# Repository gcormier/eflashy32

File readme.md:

# eflashy32

eflashy32 is a USB Type-C, CP2102N serial interface targeting ESP devices. It has a 500mA resettable fuse, ESD protection, and a switch to choose if you want to send 3.3V to the device or not.

While Micro USB is still everywhere, USB-C needs to start taking over. My new laptop has only USB-C ports, and I wanted to have one less dongle.

The board is designed in a such a manner to allow either a 2.54mm pitch 1x6 pin header, 1.27mm pitch header, or pogo pins!

## Tindie
Available <a href="https://www.tindie.com/products/gcormier/eflashy32/">for purchase on Tindie</a>.

## Design Goals
- [ ] USB Type C
- [ ] Good serial chip with no drivers needed and no <a href="https://hackaday.com/2016/02/01/ftdi-drivers-break-fake-chips-again/">malware</a>
- [ ] Switch to toggle providing power to device
- [ ] Small
- [ ] Ability to use pogo pins

## Notes
I added the ubiquitous 2.54mm pitch header for classic scenarios, using either a 6 pin header, or using 6 pogo pins. On the back side is a similar 1.27mm pitch header for miniature designs.

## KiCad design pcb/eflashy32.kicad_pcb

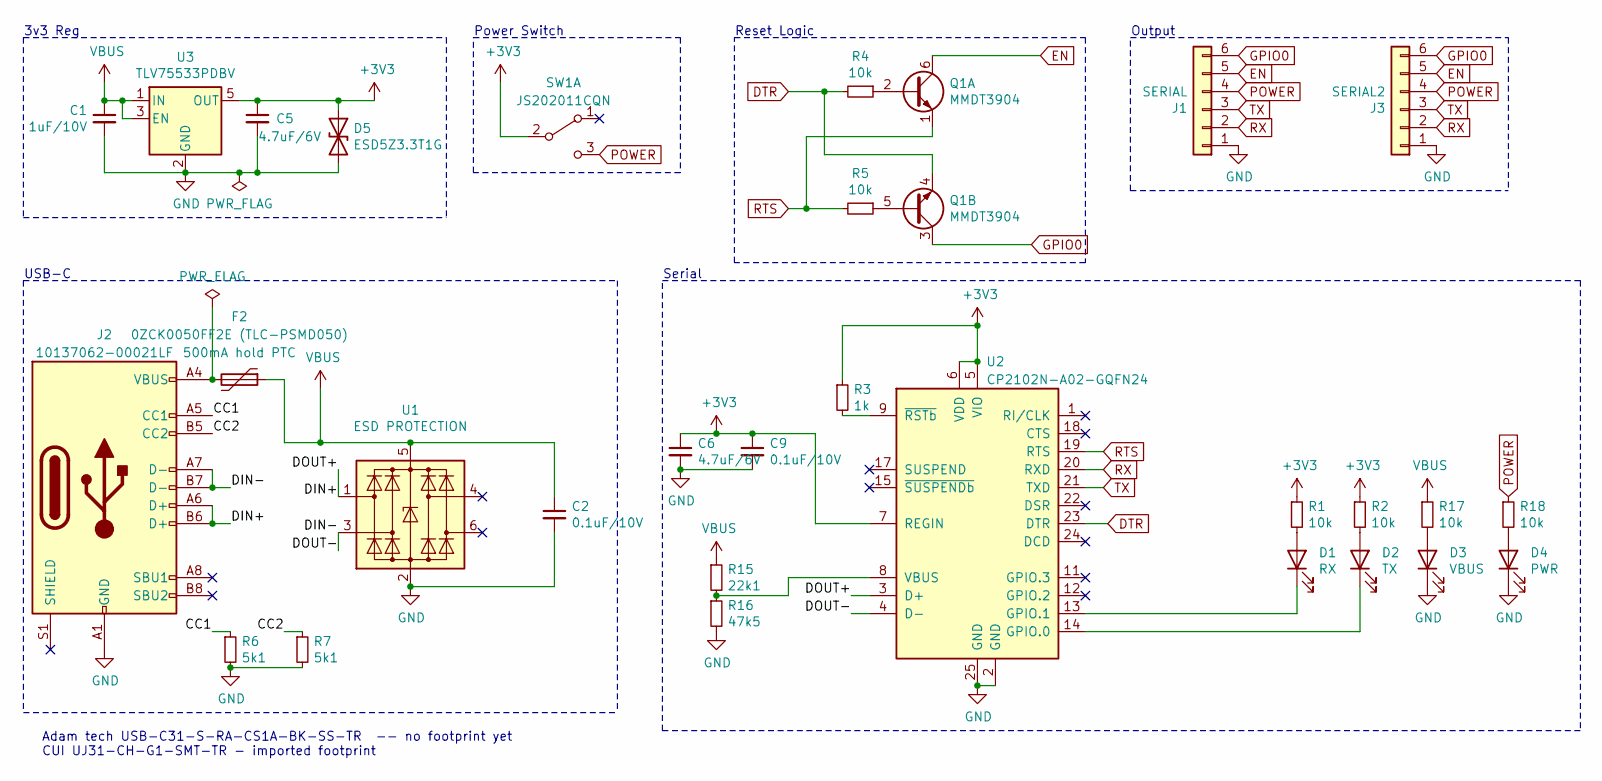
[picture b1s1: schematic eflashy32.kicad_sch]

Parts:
C1: 1uF/10V; C_0805_2012Metric; LCSC C28323
C2, C9: 0.1uF/10V; C_0805_2012Metric; LCSC C49678
C5, C6: 4.7uF/6V; C_0805_2012Metric; LCSC C1779
D1: RX; LED_0805_2012Metric; LCSC C2293
D2: TX; LED_0805_2012Metric; LCSC C2293
D3: VBUS; LED_0805_2012Metric; LCSC C2297
D4: PWR; LED_0805_2012Metric; LCSC C84256
D5: ESD5Z3.3T1G; D_SOD-523; LCSC C61148
F2: 0ZCK0050FF2E (TLC-PSMD050); Fuse_0805_2012Metric_Pad1.15x1.40mm_HandSolder; LCSC C261942
J1: SERIAL; 2.54mmedge; LCSC DNP
J2: 10137062-00021LF; USBC-Amphenol-10137062-00021LF; LCSC C388659
J3: SERIAL2; 1.27mmedge; LCSC DNP
Q1: MMDT3904; SOT-363_SC-70-6; LCSC C83572
R1, R2, R4, R5, R17, R18: 10k; R_0805_2012Metric; LCSC C17414
R3: 1k; R_0805_2012Metric; LCSC C17513
R6, R7: 5k1; R_0805_2012Metric; LCSC C27834
R15: 22k1; R_0805_2012Metric; LCSC C17560
R16: 47k5; R_0805_2012Metric; LCSC C17713
SW1: JS202011CQN; SW_CuK_JS202011CQN_DPDT_Straight; LCSC DNP
U1: ESD PROTECTION; SOT-23-6; LCSC C294963
U2: CP2102N-A02-GQFN24; QFN-24-1EP_4x4mm_P0.5mm_EP2.6x2.6mm; LCSC C969151
U3: TLV75533PDBV; SOT-23-5; LCSC C255621 C404027

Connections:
+3V3: C5.1, C6.1, C9.1, D5.1 (A1), R1.1, R2.1, R3.1, SW1.2 (B), U2.5 (VIO), U2.6 (VDD), U2.7 (REGIN), U3.5 (OUT)
/CC1: J2.A5 (CC1), R6.1
/CC2: J2.B5 (CC2), R7.1
/DIN+: J2.A6 (D+), J2.B6 (D+), U1.1 (I/O1), U2.3 (D+)
/DIN-: J2.A7 (D-), J2.B7 (D-), U1.3 (I/O2), U2.4 (D-)
DTR: Q1.4 (E2), R4.2, U2.23 (DTR)
EN: J1.5, J3.5, Q1.6 (C1)
GND: C1.2, C2.2, C5.2, C6.2, C9.2, D3.1 (K), D4.1 (K), D5.2 (A2), J1.1, J2.A1 (GND), J2.A12 (GND), J2.B1 (GND), J2.B12 (GND), J3.1, R6.2, R7.2, R16.2, U1.2 (GND), U2.2 (GND), U2.25 (GND), U3.2 (GND)
GPIO0: J1.6, J3.6, Q1.3 (C2)
unnamed: D1.1 (K), U2.13 (GPIO.1)
unnamed: D1.2 (A), R1.2
unnamed: D2.1 (K), U2.14 (GPIO.0)
unnamed: D2.2 (A), R2.2
unnamed: D3.2 (A), R17.2
unnamed: D4.2 (A), R18.2
unnamed: F2.2, J2.A4 (VBUS), J2.A9 (VBUS), J2.B4 (VBUS), J2.B9 (VBUS)
unnamed: Q1.2 (B1), R4.1
unnamed: Q1.5 (B2), R5.1
unnamed: R3.2, U2.9 (~RSTb)
unnamed: R15.2, R16.1, U2.8 (VBUS)
POWER: J1.4, J3.4, R18.1, SW1.3 (C)
RTS: Q1.1 (E1), R5.2, U2.19 (RTS)
RX: J1.2, J3.2, U2.20 (RXD)
TX: J1.3, J3.3, U2.21 (TXD)
VBUS: C1.1, C2.1, F2.1, R15.1, R17.1, U1.5 (VBUS), U3.1 (IN), U3.3 (EN)

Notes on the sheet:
3v3 Reg
USB-C
Adam tech USB-C31-S-RA-CS1A-BK-SS-TR -- no footprint yet CUI UJ31-CH-G1-SMT-TR - imported footprint
Power Switch
Serial
Reset Logic
Output

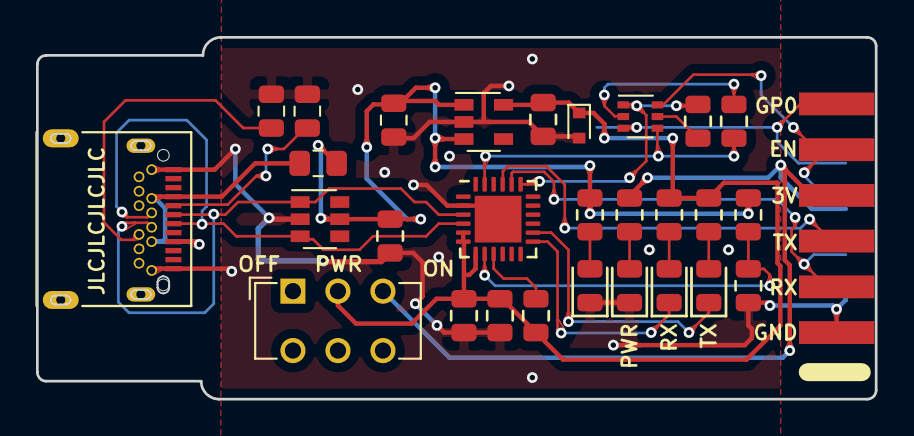
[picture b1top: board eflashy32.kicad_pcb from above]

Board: 2 copper layers, 46.6 x 20.1 mm, 30 parts (1 on the bottom side), 25 nets.

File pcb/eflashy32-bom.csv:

Comment,Designator,Footprint,LCSC
"1uF/10V","C1","Capacitor_SMD:C_0805_2012Metric","C28323"
"0.1uF/10V","C2,C9","Capacitor_SMD:C_0805_2012Metric","C49678"
"4.7uF/6V","C5,C6","Capacitor_SMD:C_0805_2012Metric","C1779"
"RX","D1","LED_SMD:LED_0805_2012Metric","C2293"
"TX","D2","LED_SMD:LED_0805_2012Metric","C2293"
"VBUS","D3","LED_SMD:LED_0805_2012Metric","C2297"
"PWR","D4","LED_SMD:LED_0805_2012Metric","C84256"
"ESD5Z3.3T1G","D5","Diode_SMD:D_SOD-523","C61148"
"0ZCK0050FF2E (TLC-PSMD050)","F2","Fuse:Fuse_0805_2012Metric_Pad1.15x1.40mm_HandSolder","C261942"
"SERIAL","J1","!Greg:2.54mmedge","DNP"
"10137062-00021LF","J2","!Greg:USBC-Amphenol-10137062-00021LF","DNP"
"SERIAL2","J3","!Greg:1.27mmedge","DNP"
"MMDT3904","Q1","Package_TO_SOT_SMD:SOT-363_SC-70-6","C83572"
"22k1","R15","Resistor_SMD:R_0805_2012Metric","C17560"
"47k5","R16","Resistor_SMD:R_0805_2012Metric","C17713"
"5k1","R6,R7,R17","Resistor_SMD:R_0805_2012Metric","C17513"
"1k","R1,R2,R3,R18","Resistor_SMD:R_0805_2012Metric","C17414"
"10k","R4,R5","Resistor_SMD:R_0805_2012Metric","C27834"
"JS202011CQN","SW1","Button_Switch_THT:SW_CuK_JS202011CQN_DPDT_Straight","DNP"
"ESD PROTECTION","U1","Package_TO_SOT_SMD:SOT-23-6","C294963"
"CP2102N-A02-GQFN24","U2","Package_DFN_QFN:QFN-24-1EP_4x4mm_P0.5mm_EP2.6x2.6mm","???"
"TLV75533PDBV","U3","Package_TO_SOT_SMD:SOT-23-5","C255621 C404027"

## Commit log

2020-07-22 software for bulk changes to cp2102n
2020-07-22 don't ignore bom
2020-07-22 stuff
2020-07-23 updated bom with lcsc for jellybeans
2020-07-23 prejig
2020-07-23 change to 4 line
2020-08-02 fixes
2020-08-04 flashing file
2020-08-04 flash script
2020-08-04 readme
2020-08-04 docs
2020-08-04 more docs
2020-08-04 flash notes
2020-08-04 formatting
